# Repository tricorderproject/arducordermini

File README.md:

Arducorder Mini
======

Arducorder Mini -- an Arduino-compatible Open Source Science Tricorder Project  
http://www.tricorderproject.org  
Copyright (C) 2014  Peter Jansen and the Tricorder project  
peter@tricorderproject.org  

*This is a work in progress*

# Introduction

This is the third iteration of the Open Source Science Tricorder prototypes, a series of science tricorder-like devices.  

Unlike the first two prototypes, this version has been designed from the ground up to be easy to manufacture, and to foster a community of open source developers and users.  The firmware is Arduino-compatible through the ChipKit MAX32 platform, and is being designed to provide advanced functionality for scientific use while being easy enough for beginners to meaningfully modify. 

# Concept
It is my deep belief that knowledge brings about positive change. 

We could live in a world where the same instrument that can show a child how much chlorophyll is in a leaf could also show how them much pollution is in the air around us, or given off by one's car. As an educator and a researcher, I feel that if people could easily discover things about their worlds that were also important social topics, that they would then make positive social choices, like reducing their emissions, or petitioning for cleaner industry in their communities. 

By having access to general inexpensive sensing tools, people can learn about healthy leaves, clean air, clouds and the water cycle, energy efficient homes — and visualize abstract concepts like spectra or magnetism. 

As a tool for exploration, we can discover things around us that we don't already know. And that's what it's about. Little discoveries, everywhere.

# Open Source

This project is open hardware and is released under various open licenses.  Please see LICENSES.TXT for details.

# Warning

**DISCLAIMER OF WARRANTIES AND LIMITATION OF LIABILITY.**

UNLESS OTHERWISE SEPARATELY UNDERTAKEN BY THE LICENSOR, TO THE EXTENT POSSIBLE, THE LICENSOR OFFERS THE LICENSED MATERIAL AS-IS AND AS-AVAILABLE, AND MAKES NO REPRESENTATIONS OR WARRANTIES OF ANY KIND CONCERNING THE LICENSED MATERIAL, WHETHER EXPRESS, IMPLIED, STATUTORY, OR OTHER. THIS INCLUDES, WITHOUT LIMITATION, WARRANTIES OF TITLE, MERCHANTABILITY, FITNESS FOR A PARTICULAR PURPOSE, NON-INFRINGEMENT, ABSENCE OF LATENT OR OTHER DEFECTS, ACCURACY, OR THE PRESENCE OR ABSENCE OF ERRORS, WHETHER OR NOT KNOWN OR DISCOVERABLE. WHERE DISCLAIMERS OF WARRANTIES ARE NOT ALLOWED IN FULL OR IN PART, THIS DISCLAIMER MAY NOT APPLY TO YOU.

TO THE EXTENT POSSIBLE, IN NO EVENT WILL THE LICENSOR BE LIABLE TO YOU ON ANY LEGAL THEORY (INCLUDING, WITHOUT LIMITATION, NEGLIGENCE) OR OTHERWISE FOR ANY DIRECT, SPECIAL, INDIRECT, INCIDENTAL, CONSEQUENTIAL, PUNITIVE, EXEMPLARY, OR OTHER LOSSES, COSTS, EXPENSES, OR DAMAGES ARISING OUT OF THIS PUBLIC LICENSE OR USE OF THE LICENSED MATERIAL, EVEN IF THE LICENSOR HAS BEEN ADVISED OF THE POSSIBILITY OF SUCH LOSSES, COSTS, EXPENSES, OR DAMAGES. WHERE A LIMITATION OF LIABILITY IS NOT ALLOWED IN FULL OR IN PART, THIS LIMITATION MAY NOT APPLY TO YOU.

THE DISCLAIMER OF WARRANTIES AND LIMITATION OF LIABILITY PROVIDED ABOVE SHALL BE INTERPRETED IN A MANNER THAT, TO THE EXTENT POSSIBLE, MOST CLOSELY APPROXIMATES AN ABSOLUTE DISCLAIMER AND WAIVER OF ALL LIABILITY.

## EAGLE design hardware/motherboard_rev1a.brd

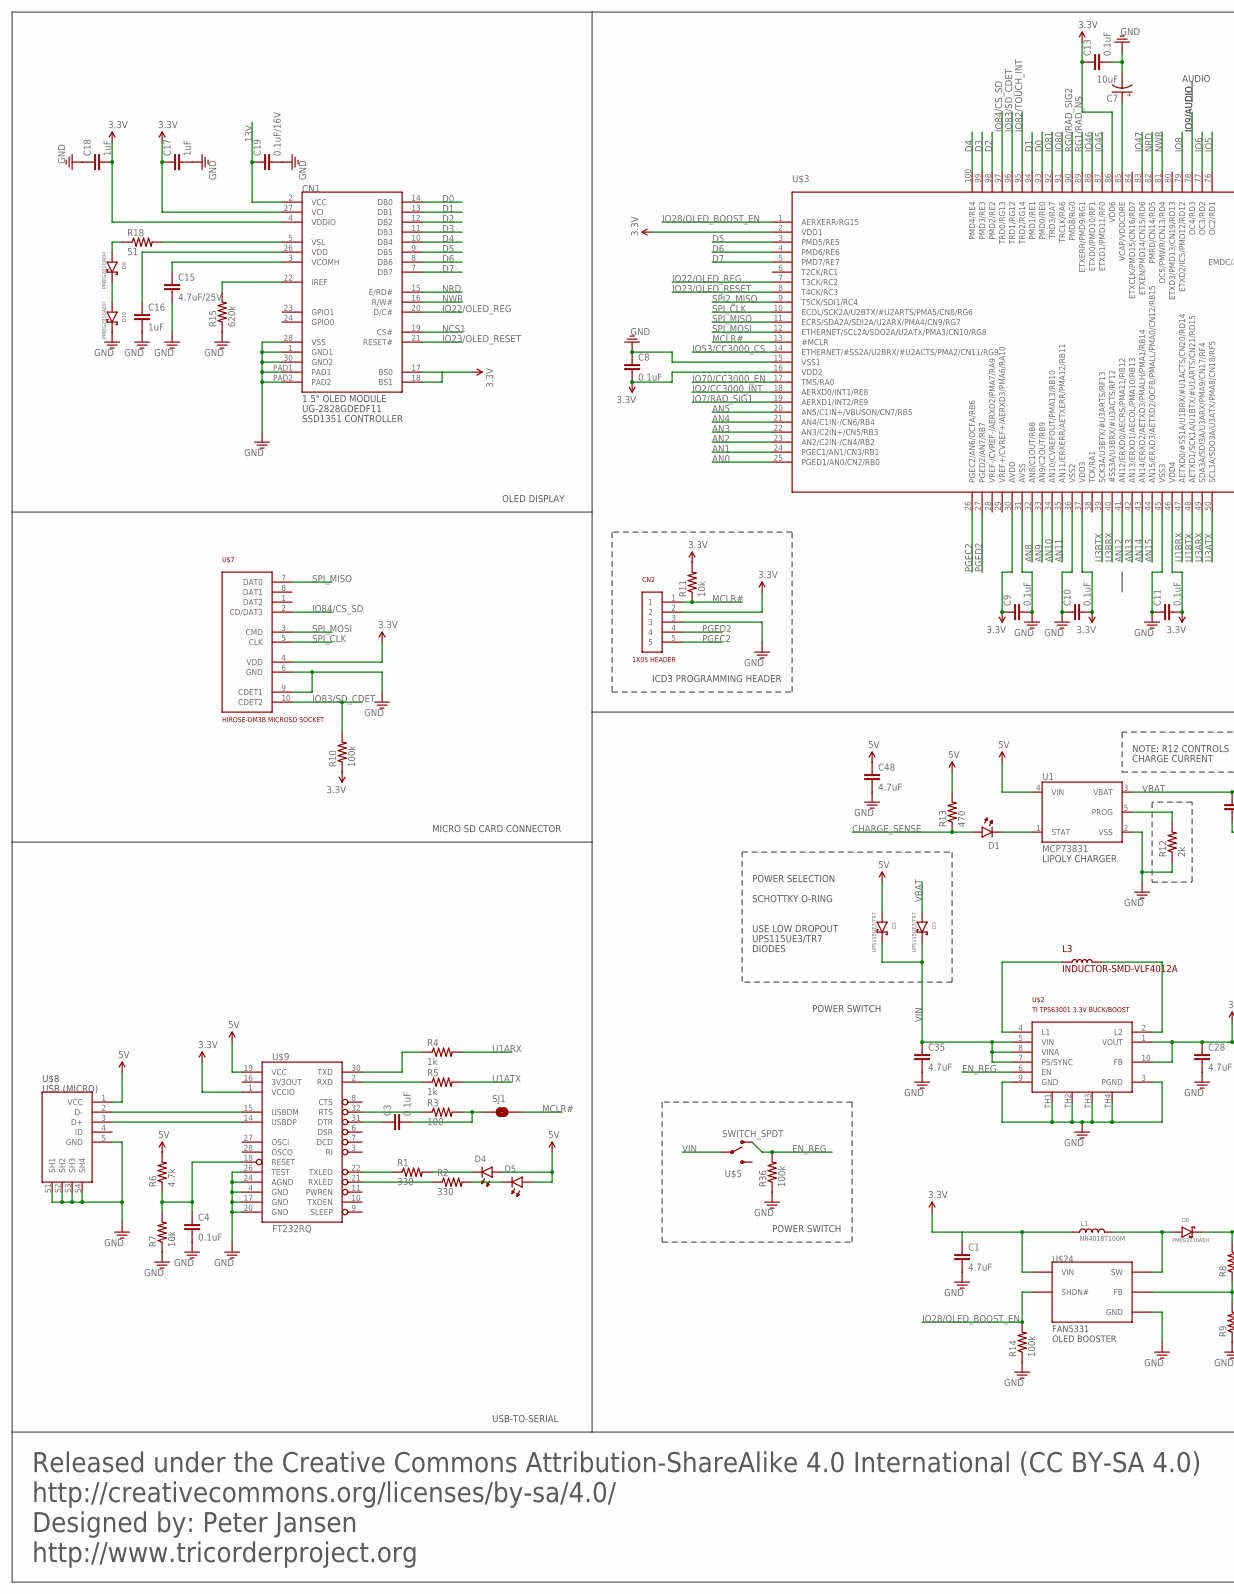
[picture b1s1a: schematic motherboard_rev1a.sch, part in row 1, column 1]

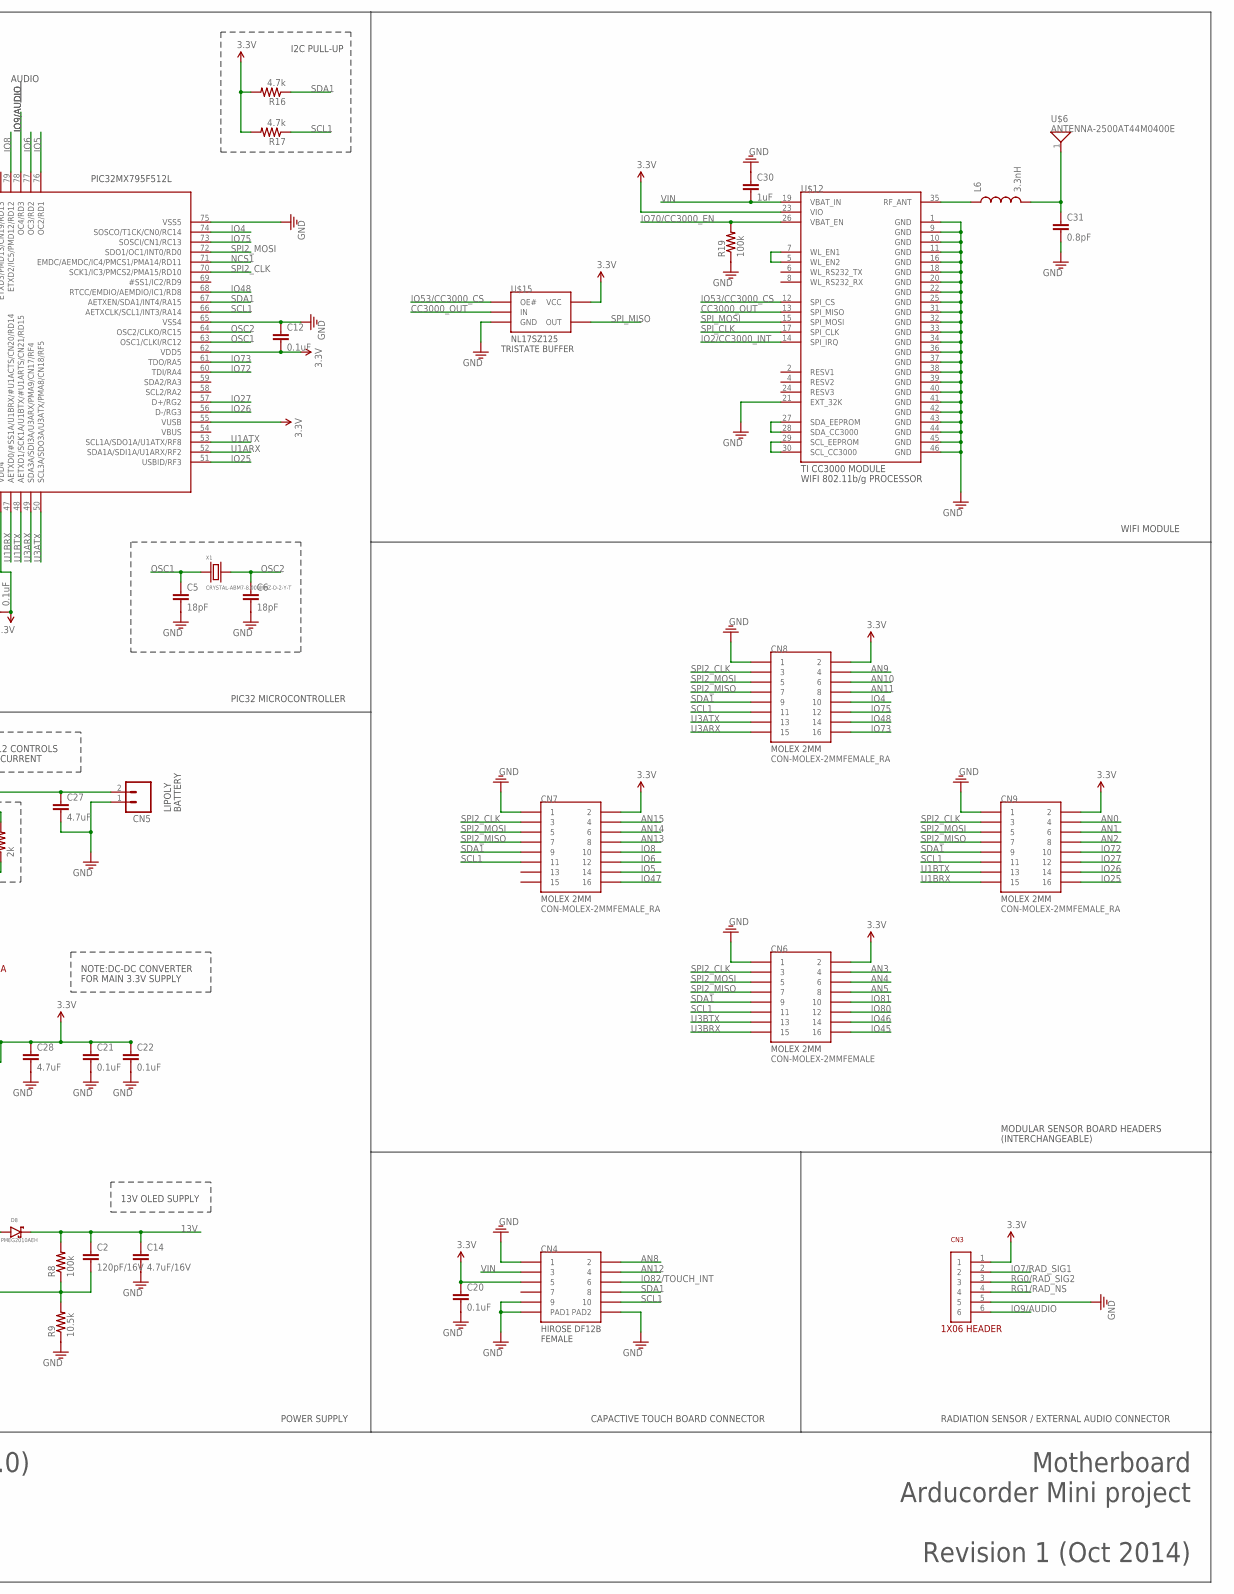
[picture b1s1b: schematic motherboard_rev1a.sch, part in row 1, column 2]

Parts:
C1, C27, C28, C35, C48: 4.7uF; 0603
C2: 120pF/16V; 0603
C3, C4, C8, C9, C10, C11, C12, C13, C20, C21, C22: 0.1uF; 0603
C5, C6: 18pF; 0603
C7: 10uF; EIA3216
C14: 4.7uF/16V; 0603
C15: 4.7uF/25V; 0603
C16, C17, C18, C30: 1uF; 0603
C19: 0.1uF/16V; 0603
C31: 0.8pF; C0402
CN1: UG-2828GDEDF11-1.5OLED; XF2M-3015-1A-1.5LCD
CN2: 1X05
CN3: PHF-106-01-L-S; 1X06
CN4: FEMALE; DF12B(3.0)-10DP-0.5V(86)
CN5: M02-JST-2MM-SMT; JST-2-SMD
CN6: CON-MOLEX-2MMFEMALE; MOLEX-0791091007
CN7, CN8, CN9: CON-MOLEX-2MMFEMALE_RA; MOLEX-87368-1624
D1, D4, D5: 0605-LED; 0603-LED
D2, D3: UPS115UE3/TR7; DO-214BA
D8, D9, D10: PMEG2010AEH; SOD123F
L1: NR4018T100M
L3: INDUCTOR-SMD-VLF4012A; VLF4012A
L6: 3.3nH; C0402
R1, R2: 330; 0603
R3: 100; 0603
R4, R5: 1k; 0603
R6, R16, R17: 4.7k; 0603
R7, R11: 10k; 0603
R8, R10, R14, R19, R36: 100k; 0603
R9: 10.5k; 0603
R12: 2k; 0603
R13: 470; 0603
R15: 620k; 0603
R18: 51; 0603
SJ1: SOLDERJUMPERTRACE; SJ_2S-TRACE
U1: MCP73831; SOT23-5
U$2: TI-TPS63001-3.3V-BUCKBOOST; TPS63001
U$3: PIC32MX795F512L-80I/PF; SQFP-S-14X14-100
U$5: SWITCH_SPDT; KPS-1290
U$6: ANTENNA-2500AT44M0400E; ANT-2500AT44M0400E
U$7: CON-HIROSE-DM3B-MICROSD
U$8: USB-MICROB; FCI-10104110-0001LF
U$9: FT232RQ; QFN-32
U$12: CC3000
U$15: BUFFER-NL17SZ125; TSOP-5
U$24: FAN5331-BOOST; TSOP-5
X1: CRYSTAL-ABM7-8.000MHZ-D-2-Y-T; CYRSTAL-6.0X3.5MM

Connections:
3.3V: C1.1, C8.2, C9.1, C10.2, C11.2, C12.2, C13.1, C17.1, C18.2, C20.1, C21.1, C22.1, C28.1, CN1.4 (VDDIO), CN1.17 (BS0), CN1.18 (BS1), CN1.27 (VCI), CN2.2, CN3.1, CN4.5, CN6.2, CN7.2, CN8.2, CN9.2, L1.2, R10.1, R11.2, R16.2, R17.2, U$2.1 (VOUT), U$2.10 (FB), U$3.2 (VDD1), U$3.16 (VDD2), U$3.30 (AVDD), U$3.37 (VDD3), U$3.46 (VDD4), U$3.55 (VUSB), U$3.62 (VDD5), U$3.86 (VDD6), U$7.4 (VDD), U$9.1 (VCCIO), U$12.23 (VIO), U$15.5 (VCC), U$24.5 (VIN)
5V: C48.1, D2.ANODE, D4.ANODE, D5.ANODE, R6.2, R13.2, U1.4 (VIN), U$8.1 (VCC), U$9.19 (VCC)
13V: C2.1, C14.1, C19.1, CN1.2 (VCC), D8.1 (CATHODE), R8.2
AN0: CN9.4, U$3.25 (PGED1/AN0/CN2/RB0)
AN1: CN9.6, U$3.24 (PGEC1/AN1/CN3/RB1)
AN2: CN9.8, U$3.23 (AN2/C2IN-/CN4/RB2)
AN3: CN6.4, U$3.22 (AN3/C2IN+/CN5/RB3)
AN4: CN6.6, U$3.21 (AN4/C1IN-/CN6/RB4)
AN5: CN6.8, U$3.20 (AN5/C1IN+/VBUSON/CN7/RB5)
AN8: CN4.2, U$3.32 (AN8/C1OUT/RB8)
AN9: CN8.4, U$3.33 (AN9/C2OUT/RB9)
AN10: CN8.6, U$3.34 (AN10/CVREFOUT/PMA13/RB10)
AN11: CN8.8, U$3.35 (AN11/ERXERR/AETXERR/PMA12/RB11)
AN12: CN4.4, U$3.41 (AN12/ERXD0/AECRS/PMA11/RB12)
AN13: CN7.8, U$3.42 (AN13/ERXD1/AECOL/PMA10/RB13)
AN14: CN7.6, U$3.43 (AN14/ERXD2/AETXD3/PMALH/PMA1/RB14)
AN15: CN7.4, U$3.44 (AN15/ERXD3/AETXD2/OCFB/PMALL/PMA0/CN12/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)
CC3000_OUT: U$12.13 (SPI_MISO), U$15.2 (IN)
CHARGE_SENSE: D1.ANODE, R13.1
D0: CN1.14 (DB0), U$3.93 (PMD0/RE0)
D1: CN1.13 (DB1), U$3.94 (PMD1/RE1)
D2: CN1.12 (DB2), U$3.98 (PMD2/RE2)
D3: CN1.11 (DB3), U$3.99 (PMD3/RE3)
D4: CN1.10 (DB4), U$3.100 (PMD4/RE4)
D5: CN1.9 (DB5), U$3.3 (PMD5/RE5)
D6: CN1.8 (DB6), U$3.4 (PMD6/RE6)
D7: CN1.7 (DB7), U$3.5 (PMD7/RE7)
EN_REG: R36.2, U$2.6 (EN), U$5.O
GND: C1.2, C4.2, C5.2, C6.2, C7.C (-), C8.1, C9.2, C10.1, C11.1, C12.1, C13.2, C14.2, C15.2, C16.2, C17.2, C18.1, C19.2, C20.2, C21.2, C22.2, C27.2, C28.2, C30.1, C31.2, C35.2, C48.2, CN1.1 (GND1), CN1.28 (VSS), CN1.30 (GND2), CN1.PAD1, CN1.PAD2, CN2.3, CN3.5, CN4.1, CN4.9, CN4.PAD1, CN4.PAD2, CN5.1 (2), CN6.1, CN7.1, CN8.1, CN9.1, D10.1 (CATHODE), R7.1, R9.1, R12.1, R14.1, R15.1, R19.1, R36.1, U1.2 (VSS), U$2.3 (PGND), U$2.9 (GND), U$2.TH1 (THERM1), U$2.TH2 (THERM2), U$2.TH3 (THERM3), U$2.TH4 (THERM4), U$3.15 (VSS1), U$3.31 (AVSS), U$3.36 (VSS2), U$3.45 (VSS3), U$3.65 (VSS4), U$3.75 (VSS5), U$7.6 (GND), U$7.9 (CDET1), U$8.5 (GND), U$8.S1 (SH1), U$8.S2 (SH2), U$8.S3 (SH3), U$8.S4 (SH4), U$9.4 (GND), U$9.17 (GND), U$9.20 (GND), U$9.24 (AGND), U$9.26 (TEST), U$12.1 (GND), U$12.9 (GND), U$12.10 (GND), U$12.11 (GND), U$12.16 (GND), U$12.18 (GND), U$12.20 (GND), U$12.21 (EXT_32K), U$12.22 (GND), U$12.25 (GND), U$12.31 (GND), U$12.32 (GND), U$12.33 (GND), U$12.34 (GND), U$12.36 (GND), U$12.37 (GND), U$12.38 (GND), U$12.39 (GND), U$12.40 (GND), U$12.41 (GND), U$12.42 (GND), U$12.43 (GND), U$12.44 (GND), U$12.45 (GND), U$12.46 (GND), U$15.3 (GND), U$24.2 (GND)
IO2/CC3000_INT: U$3.18 (AERXD0/INT1/RE8), U$12.14 (SPI_IRQ)
IO4: CN8.10, U$3.74 (SOSCO/T1CK/CN0/RC14)
IO5: CN7.14, U$3.76 (OC2/RD1)
IO6: CN7.12, U$3.77 (OC3/RD2)
IO7/RAD_SIG1: CN3.2, U$3.19 (AERXD1/INT2/RE9)
IO8: CN7.10, U$3.79 (ETXD2/IC5/PMD12/RD12)
IO9/AUDIO: CN3.6, U$3.78 (OC4/RD3)
IO22/OLED_REG: CN1.20 (D/C#), U$3.7 (T3CK/RC2)
IO23/OLED_RESET: CN1.21 (RESET#), U$3.8 (T4CK/RC3)
IO25: CN9.16, U$3.51 (USBID/RF3)
IO26: CN9.14, U$3.56 (D-/RG3)
IO27: CN9.12, U$3.57 (D+/RG2)
IO28/OLED_BOOST_EN: R14.2, U$3.1 (AERXERR/RG15), U$24.4 (SHDN#)
IO45: CN6.16, U$3.87 (ETXD1/PMD11/RF0)
IO46: CN6.14, U$3.88 (ETXD0/PMD10/RF1)
IO47: CN7.16, U$3.83 (ETXEN/PMD14/CN15/RD6)
IO48: CN8.14, U$3.68 (RTCC/EMDIO/AEMDIO/IC1/RD8)
IO53/CC3000_CS: U$3.14 (ETHERNET/#SS2A/U2BRX/#U2ACTS/PMA2/CN11/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), U$12.12 (SPI_CS), U$15.1 (OE#)
IO70/CC3000_EN: R19.2, U$3.17 (TMS/RA0), U$12.26 (VBAT_EN)
IO72: CN9.10, U$3.60 (TDI/RA4)
IO73: CN8.16, U$3.61 (TDO/RA5)
IO75: CN8.12, U$3.73 (SOSCI/CN1/RC13)
IO80: CN6.12, U$3.91 (TRCLK/RA6)
IO81: CN6.10, U$3.92 (TRD3/RA7)
IO82/TOUCH_INT: CN4.6, U$3.95 (TRD2/RG14)
IO83/SD_CDET: R10.2, U$3.96 (TRD1/RG12), U$7.10 (CDET2)
IO84/CS_SD: U$3.97 (TRD0/RG13), U$7.2 (CD/DAT3)
MCLR#: CN2.1, R11.1, SJ1.2, U$3.13 (#MCLR)
unnamed: L3.1, U$2.4 (L1)
unnamed: L3.2, U$2.2 (L2)
unnamed: U$8.2 (D-), U$9.15 (USBDM)
unnamed: U$8.3 (D+), U$9.14 (USBDP)
unnamed: R1.1, U$9.22 (TXLED)
unnamed: R2.1, U$9.21 (RXLED)
unnamed: D4.CATHODE, R1.2
unnamed: D5.CATHODE, R2.2
unnamed: C3.1, U$9.31 (DTR)
unnamed: R3.1, U$9.32 (RTS)
unnamed: C3.2, R3.2, SJ1.1
unnamed: C4.1, R6.1, R7.2, U$9.18 (RESET)
unnamed: R5.1, U$9.2 (RXD)
unnamed: C31.1, L6.2, U$6.1
unnamed: R4.1, U$9.30 (TXD)
unnamed: U$12.27 (SDA_EEPROM), U$12.28 (SDA_CC3000)
unnamed: L6.1, U$12.35 (RF_ANT)
unnamed: C7.A (+), U$3.85 (VCAP/VDDCORE)
unnamed: C15.1, CN1.3 (VCOMH)
unnamed: D8.2 (ANODE), L1.1, U$24.1 (SW)
unnamed: CN1.22 (IREF), R15.2
unnamed: C2.2, R8.1, R9.2, U$24.3 (FB)
unnamed: C16.1, CN1.26 (VDD)
unnamed: D9.1 (CATHODE), D10.2 (ANODE)
unnamed: D9.2 (ANODE), R18.1
unnamed: R12.2, U1.5 (PROG)
unnamed: U$12.29 (SCL_EEPROM), U$12.30 (SCL_CC3000)
unnamed: CN1.5 (VSL), R18.2
unnamed: D1.CATHODE, U1.1 (STAT)
unnamed: U$12.5 (WL_EN2), U$12.7 (WL_EN1)
NCS1: CN1.19 (CS#), U$3.71 (EMDC/AEMDC/IC4/PMCS1/PMA14/RD11)
NRD: CN1.15 (E/RD#), U$3.82 (PMRD/CN14/RD5)
NWR: CN1.16 (R/W#), U$3.81 (OC5/PMWR/CN13/RD4)
OSC1: C5.1, U$3.63 (OSC1/CLKI/RC12), X1.1
OSC2: C6.1, U$3.64 (OSC2/CLKO/RC15), X1.2
PGEC2: CN2.5, U$3.26 (PGEC2/AN6/OCFA/RB6)
PGED2: CN2.4, U$3.27 (PGED2/AN7/RB7)
RG0/RAD_SIG2: CN3.3, U$3.90 (PMD8/RG0)
RG1/RAD_NS: CN3.4, U$3.89 (ETXERR/PMD9/RG1)
SCL1: CN4.10, CN6.11, CN7.11, CN8.11, CN9.11, R17.1, U$3.66 (AETXCLK/SCL1/INT3/RA14)
SDA1: CN4.8, CN6.9, CN7.9, CN8.9, CN9.9, R16.1, U$3.67 (AETXEN/SDA1/INT4/RA15)
SPI2_CLK: CN6.3, CN7.3, CN8.3, CN9.3, U$3.70 (SCK1/IC3/PMCS2/PMA15/RD10)
SPI2_MISO: CN6.7, CN7.7, CN8.7, CN9.7, U$3.9 (T5CK/SDI1/RC4)
SPI2_MOSI: CN6.5, CN7.5, CN8.5, CN9.5, U$3.72 (SDO1/OC1/INT0/RD0)
SPI_CLK: U$3.10 (ECOL/SCK2A/U2BTX/#U2ARTS/PMA5/CN8/RG6), U$7.5 (CLK), U$12.17 (SPI_CLK)
SPI_MISO: U$3.11 (ECRS/SDA2A/SDI2A/U2ARX/PMA4/CN9/RG7), U$7.7 (DAT0), U$15.4 (OUT)
SPI_MOSI: U$3.12 (ETHERNET/SCL2A/SDO2A/U2ATX/PMA3/CN10/RG8), U$7.3 (CMD), U$12.15 (SPI_MOSI)
U1ARX: R4.2, U$3.52 (SDA1A/SDI1A/U1ARX/RF2)
U1ATX: R5.2, U$3.53 (SCL1A/SDO1A/U1ATX/RF8)
U1BRX: CN9.15, U$3.47 (AETXD0/#SS1A/U1BRX/#U1ACTS/CN20/RD14)
U1BTX: CN9.13, U$3.48 (AETXD1/SCK1A/U1BTX/#U1ARTS/CN21/RD15)
U3ARX: CN8.15, U$3.49 (SDA3A/SDI3A/U3ARX/PMA9/CN17/RF4)
U3ATX: CN8.13, U$3.50 (SCL3A/SDO3A/U3ATX/PMA8/CN18/RF5)
U3BRX: CN6.15, U$3.40 (#SS3A/U3BRX/#U3ACTS/RF12)
U3BTX: CN6.13, U$3.39 (SCK3A/U3BTX/#U3ARTS/RF13)
VBAT: C27.1, CN5.2 (1), D3.ANODE, U1.3 (VBAT)
VIN: C30.2, C35.1, CN4.3, D2.CATHODE, D3.CATHODE, U$2.5 (VIN), U$2.7 (PS/SYNC), U$2.8 (VINA), U$5.P, U$12.19 (VBAT_IN)

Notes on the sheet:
NOTE: R12 CONTROLS
CHARGE CURRENT
POWER SELECTION
SCHOTTKY O-RING
USE LOW DROPOUT
UPS115UE3/TR7
DIODES
LIPOLY
POWER SWITCH
AUDIO
Released under the Creative Commons Attribution-ShareAlike 4.0 International (CC BY-SA 4.0)
http://creativecommons.org/licenses/by-sa/4.0/
Designed by: Peter Jansen
http://www.tricorderproject.org
Revision 1 (Oct 2014)
Arducorder Mini project
Motherboard
USB-TO-SERIAL
MICRO SD CARD CONNECTOR
OLED DISPLAY
PIC32 MICROCONTROLLER
POWER SUPPLY
LIPOLY CHARGER
NOTE:DC-DC CONVERTER
FOR MAIN 3.3V SUPPLY
13V OLED SUPPLY
BATTERY
WIFI MODULE
MODULAR SENSOR BOARD HEADERS
(INTERCHANGEABLE)
CAPACTIVE TOUCH BOARD CONNECTOR
RADIATION SENSOR / EXTERNAL AUDIO CONNECTOR
ICD3 PROGRAMMING HEADER
I2C PULL-UP

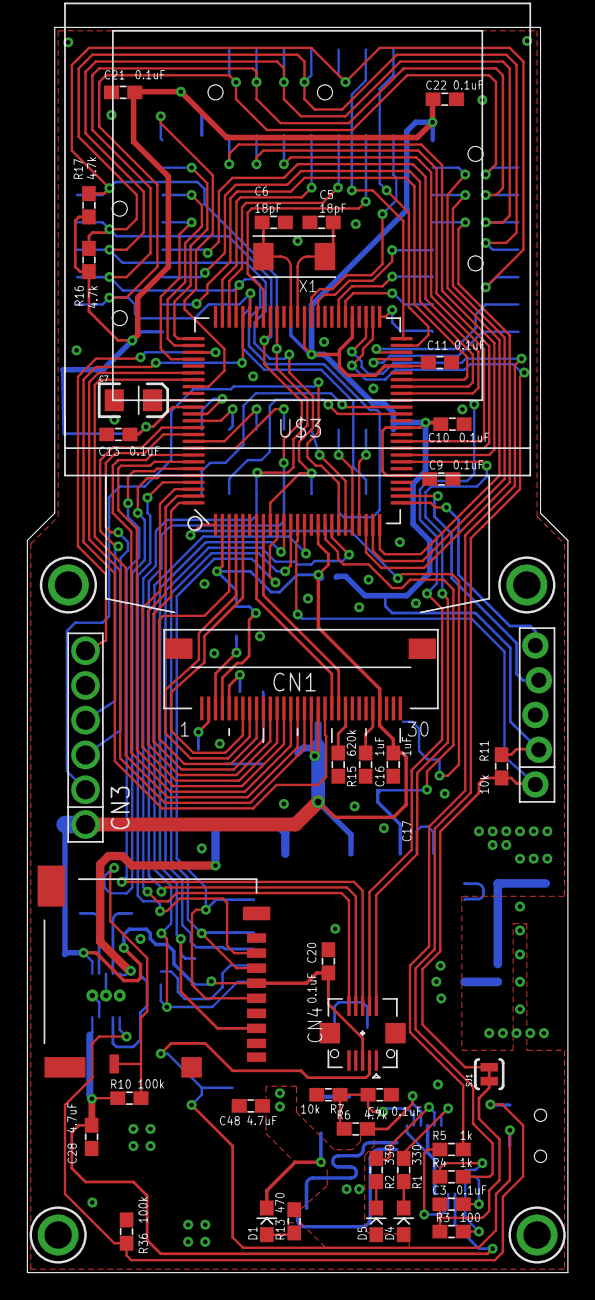
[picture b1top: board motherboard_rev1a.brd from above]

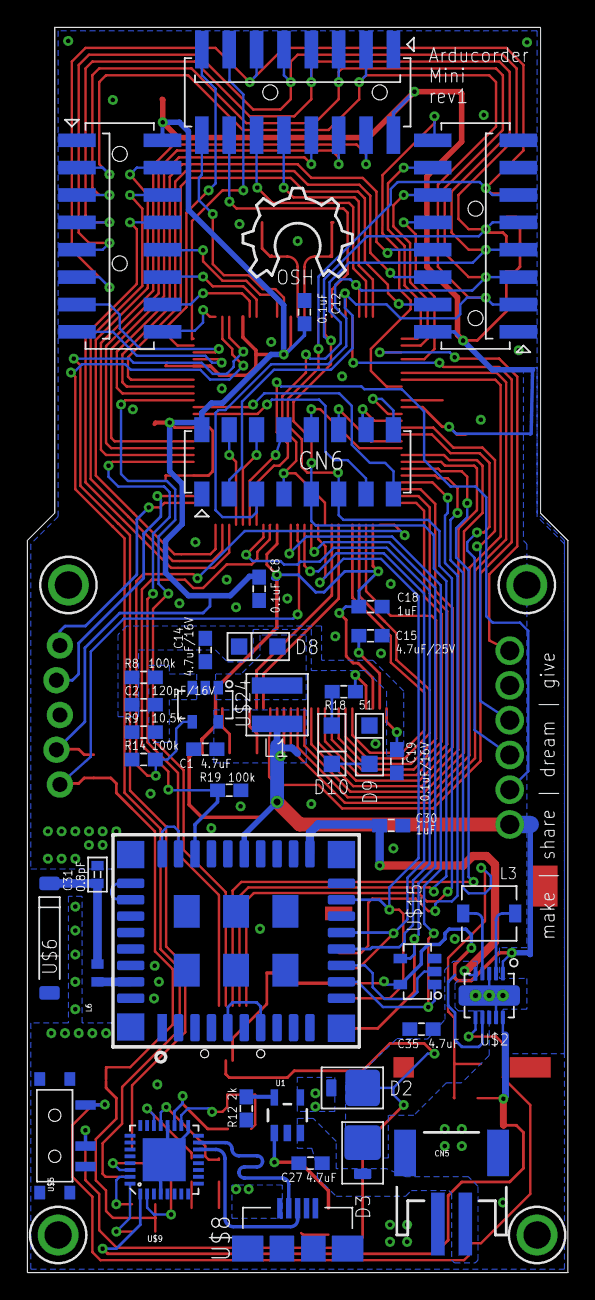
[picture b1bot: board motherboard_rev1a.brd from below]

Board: 2 copper layers, 39.5 x 91.0 mm, 81 parts (40 on the bottom side), 114 nets.

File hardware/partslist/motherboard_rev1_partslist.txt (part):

Partlist

Exported from motherboard_rev1.sch at 27/10/2014 11:52:06 PM

EAGLE Version 6.5.0 Copyright (c) 1988-2013 CadSoft

Assembly variant: 

Part     Value                         Device                        Package                  Library                    Sheet

C1       4.7uF                         CAP0603                       0603                     notes_mark5a               1
C2       120pF/16V                     CAP0603                       0603                     notes_mark5a1              1
C3       0.1uF                         CAP0603                       0603                     notes_mark5a               1
C4       0.1uF                         CAP0603                       0603                     notes_mark5a               1
C5       18pF                          CAP0603                       0603                     notes_mark5a               1
C6       18pF                          CAP0603                       0603                     notes_mark5a               1
C7       10uF                          CAP_POL1206                   EIA3216                  SparkFun-Passives          1
C8       0.1uF                         CAP0603                       0603                     notes_mark5a               1
C9       0.1uF                         CAP0603                       0603                     notes_mark5a               1
C10      0.1uF                         CAP0603                       0603                     notes_mark5a               1
C11      0.1uF                         CAP0603                       0603                     notes_mark5a               1
C12      0.1uF                         CAP0603                       0603                     notes_mark5a               1
C13      0.1uF                         CAP0603                       0603                     notes_mark5a               1
C14      4.7uF/16V                     CAP0603                       0603                     notes_mark5a               1
C15      4.7uF/25V                     CAP0603                       0603                     notes_mark5a               1
C16      1uF                           CAP0603                       0603                     notes_mark5a               1
C17      1uF                           CAP0603                       0603                     notes_mark5a               1
C18      1uF                           CAP0603                       0603                     notes_mark5a               1
C19      0.1uF/16V                     CAP0603                       0603                     notes_mark5a               1
C20      0.1uF                         CAP0603                       0603                     notes_mark5a               1
C21      0.1uF                         CAP0603                       0603                     notes_mark5a               1
C22      0.1uF                         CAP0603                       0603                     notes_mark5a               1
C27      4.7uF                         CAP0603                       0603                     notes_mark5a               1
C28      4.7uF                         CAP0603                       0603                     notes_mark5a               1
C30      1uF                           CAP0603                       0603                     notes_mark5a               1
C31      0.8pF                         CAP0402                       C0402                    notes_mark5a               1
C35      4.7uF                         CAP0603                       0603                     notes_mark5a               1
C48      4.7uF                         CAP0603                       0603                     notes_mark5a               1
CN1      UG-2828GDEDF11-1.5OLED        UG-2828GDEDF11-1.5OLED        XF2M-3015-1A-1.5LCD      notes-arducorder-mini      1
CN2      1X05                          1X05                          1X05                     notes_mark5a               1
CN3      PHF-106-01-L-S                1X06                          1X06                     arm1a                      1
CN4      FEMALE                        CON-HIROSE-DF12FEMALE         DF12B(3.0)-10DP-0.5V(86) notes-arducorder-mini      1
CN5                                    M02-JST-2MM-SMT               JST-2-SMD                SparkFun-Connectors        1
CN6      CON-MOLEX-2MMFEMALE           CON-MOLEX-2MMFEMALE           MOLEX-0791091007         notes-arducorder-mini      1
CN7      CON-MOLEX-2MMFEMALE_RA        CON-MOLEX-2MMFEMALE_RA        MOLEX-87368-1624         notes-arducorder-mini      1
CN8      CON-MOLEX-2MMFEMALE_RA        CON-MOLEX-2MMFEMALE_RA        MOLEX-87368-1624         notes-arducorder-mini      1
CN9      CON-MOLEX-2MMFEMALE_RA        CON-MOLEX-2MMFEMALE_RA        MOLEX-87368-1624         notes-arducorder-mini      1
D1       0605-LED                      0605-LED                      0603-LED                 notes_mark5a               1
D2       UPS115UE3/TR7                 DIODE-SCHOTTKY                DO-214BA                 notes_mark5a               1
D3       UPS115UE3/TR7                 DIODE-SCHOTTKY                DO-214BA                 notes_mark5a               1
D4       0605-LED                      0605-LED                      0603-LED                 notes_mark5a               1
D5       0605-LED                      0605-LED                      0603-LED                 notes_mark5a               1
D8       PMEG2010AEH                   DIODE-SCHOTTKYSOD123F         SOD123F                  notes-arducorder-mini      1
D9       PMEG2010AEH                   DIODE-SCHOTTKYSOD123F         SOD123F                  notes-arducorder-mini      1
D10      PMEG2010AEH                   DIODE-SCHOTTKYSOD123F         SOD123F                  notes-arducorder-mini      1
L1       NR4018T100M                   INDUCTORNR4018T100M           NR4018T100M              notes-arducorder-mini      1
L3       INDUCTOR-SMD-VLF4012A         INDUCTOR-SMD-VLF4012A         VLF4012A                 notes_mark5a               1
L6       3.3nH                         INDUCTOR0402                  C0402                    SparkFun-Passives          1
R1       330                           RESISTOR0603                  0603                     notes_mark5a               1
R2       330                           RESISTOR0603                  0603                     notes_mark5a               1
R3       100                           RESISTOR0603                  0603                     notes_mark5a               1
R4       1k                            RESISTOR0603                  0603                     notes_mark5a               1
R5       1k                            RESISTOR0603                  0603                     notes_mark5a               1
R6       4.7k                          RESISTOR0603                  0603                     notes_mark5a               1
R7       10k                           RESISTOR0603                  0603                     notes_mark5a               1
R8       100k                          RESISTOR0603                  0603                     notes_mark5a1              1
R9       10.5k                         RESISTOR0603                  0603                     notes_mark5a1              1
R10      100k                          RESISTOR0603                  0603                     notes_mark5a               1
R11      10k                           RESISTOR0603                  0603                     notes_mark5a               1
R12      2k                            RESISTOR0603                  0603                     notes_mark5a               1
R13      470                           RESISTOR0603                  0603                     notes_mark5a               1
R14      100k                          RESISTOR0603                  0603                     notes_mark5a1              1
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
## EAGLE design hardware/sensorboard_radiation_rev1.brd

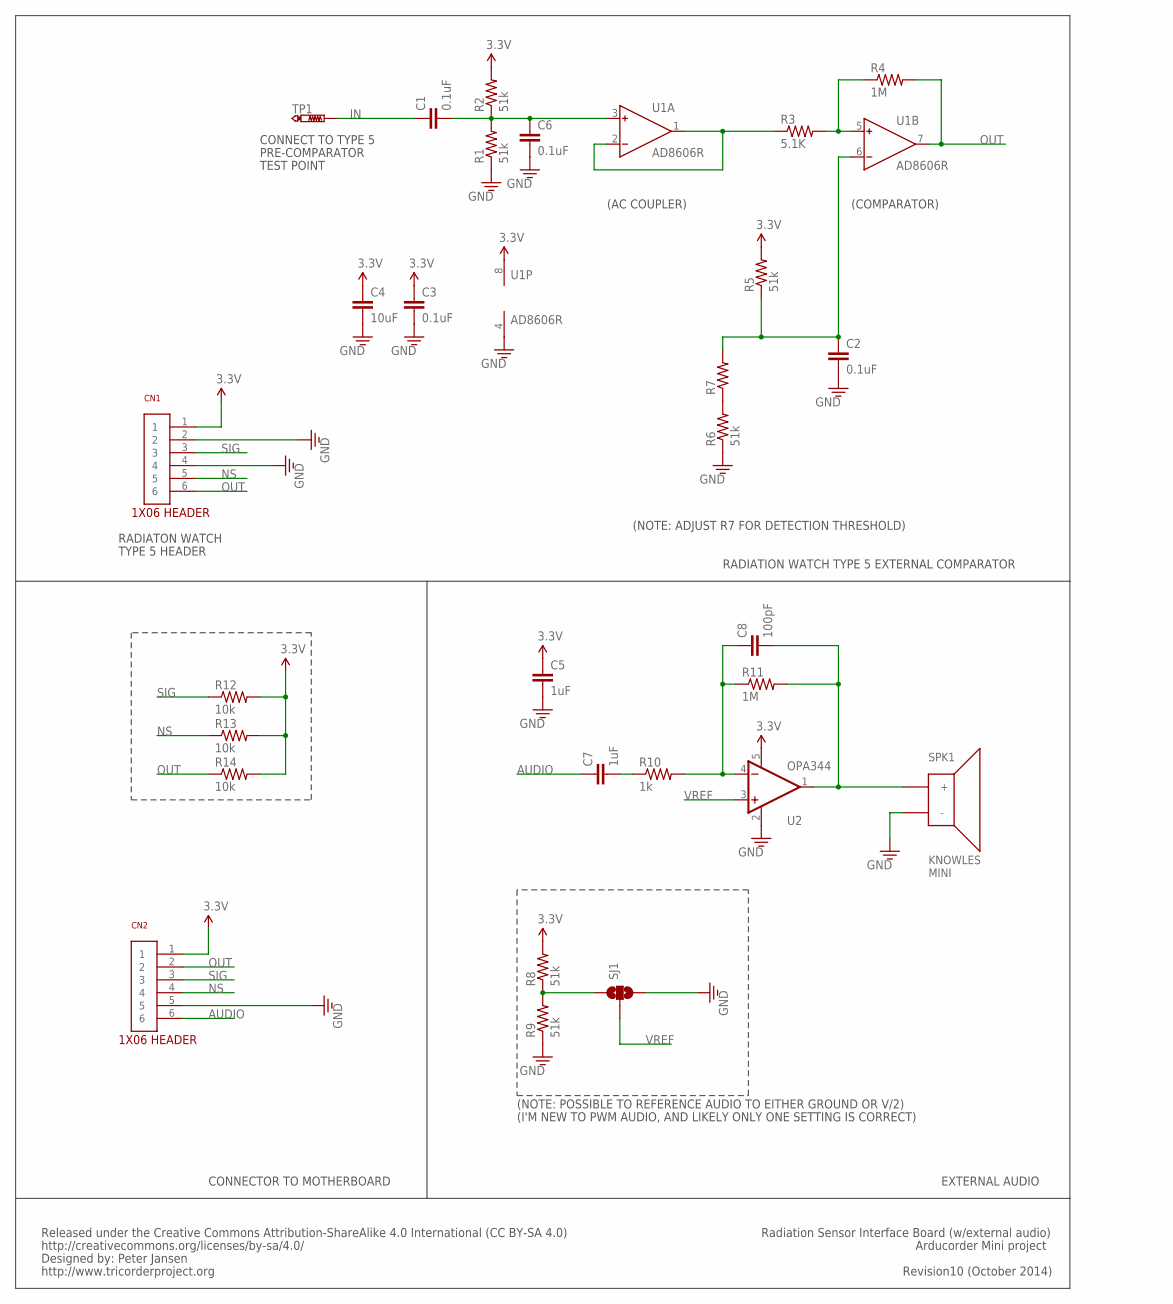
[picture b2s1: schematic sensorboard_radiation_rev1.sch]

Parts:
C1, C2, C3, C6: 0.1uF; 0603
C4: 10uF; 0603
C5, C7: 1uF; 0603
C8: 100pF; 0603
CN1: 1X06
CN2: PHT-106-01-L-S; 1X06
R1, R2, R5, R6, R8, R9: 51k; 0603
R3: 5.1K; 0603
R4, R11: 1M; 0603
R7: RESISTOR0603; 0603
R10: 1k; 0603
R12, R13, R14: 10k; 0603
SJ1: SOLDERJUMPER_2WAYPASTE1&2; SJ_3_PASTE1&2
SPK1: KNOWLES-MINI-SPEAKER
TP1: PTR1PAD1-13; P1-13
U1: AD8606R; SO8
U2: OPA344; SOT23-5

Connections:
3.3V: C3.1, C4.1, C5.1, CN1.1, CN2.1, R2.2, R5.2, R8.2, R12.2, R13.2, R14.2, U1.8 (V+), U2.5 (V+)
ADMP_OUT: C8.2, R11.2, SPK1.POS (+), U2.1 (OUT)
AUDIO: C7.1, CN2.6
GND: C2.2, C3.2, C4.2, C5.2, C6.2, CN1.2, CN1.4, CN2.5, R1.1, R6.1, R9.1, SJ1.3, SPK1.NEG (-), U1.4 (V-), U2.2 (V-)
IN: C1.1, TP1.TP
unnamed: R6.2, R7.1
unnamed: C1.2, C6.1, R1.2, R2.1, U1.3 (IN+)
unnamed: R3.1, U1.1 (OUT), U1.2 (IN-)
unnamed: R3.2, R4.1, U1.5 (IN+)
unnamed: C2.1, R5.1, R7.2, U1.6 (IN-)
unnamed: C7.2, R10.1
unnamed: C8.1, R10.2, R11.1, U2.4 (-IN)
NS: CN1.5, CN2.4, R13.1
OUT: CN1.6, CN2.2, R4.2, R14.1, U1.7 (OUT)
SIG: CN1.3, CN2.3, R12.1
VREF: SJ1.2, U2.3 (+IN)
VREF1: R8.1, R9.2, SJ1.1

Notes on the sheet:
(AC COUPLER)
(COMPARATOR)
CONNECT TO TYPE 5
PRE-COMPARATOR
TEST POINT
RADIATON WATCH
TYPE 5 HEADER
(NOTE: ADJUST R7 FOR DETECTION THRESHOLD)
(NOTE: POSSIBLE TO REFERENCE AUDIO TO EITHER GROUND OR V/2)
Released under the Creative Commons Attribution-ShareAlike 4.0 International (CC BY-SA 4.0)
http://creativecommons.org/licenses/by-sa/4.0/
Designed by: Peter Jansen
http://www.tricorderproject.org
Revision10 (October 2014)
Arducorder Mini project
Radiation Sensor Interface Board (w/external audio)
(I'M NEW TO PWM AUDIO, AND LIKELY ONLY ONE SETTING IS CORRECT)
EXTERNAL AUDIO
CONNECTOR TO MOTHERBOARD
RADIATION WATCH TYPE 5 EXTERNAL COMPARATOR

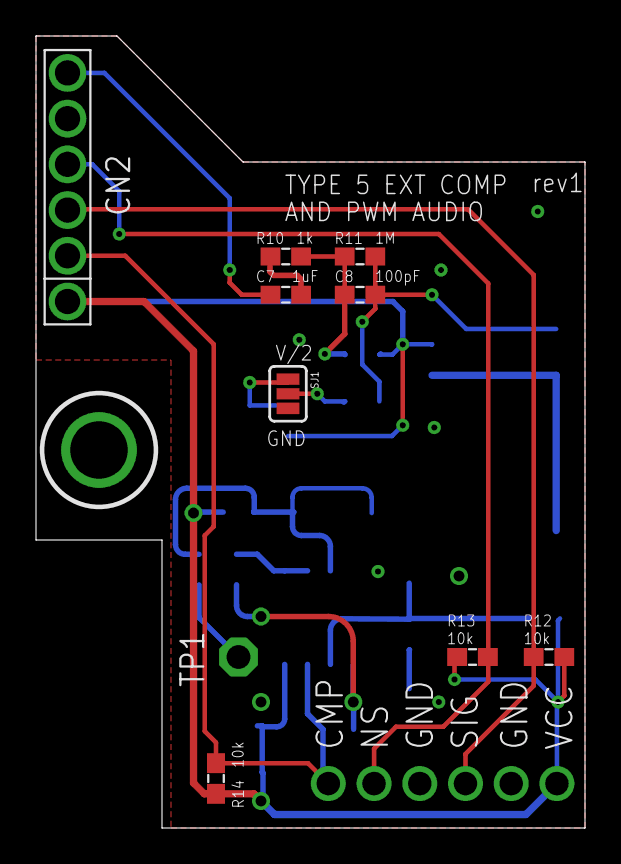
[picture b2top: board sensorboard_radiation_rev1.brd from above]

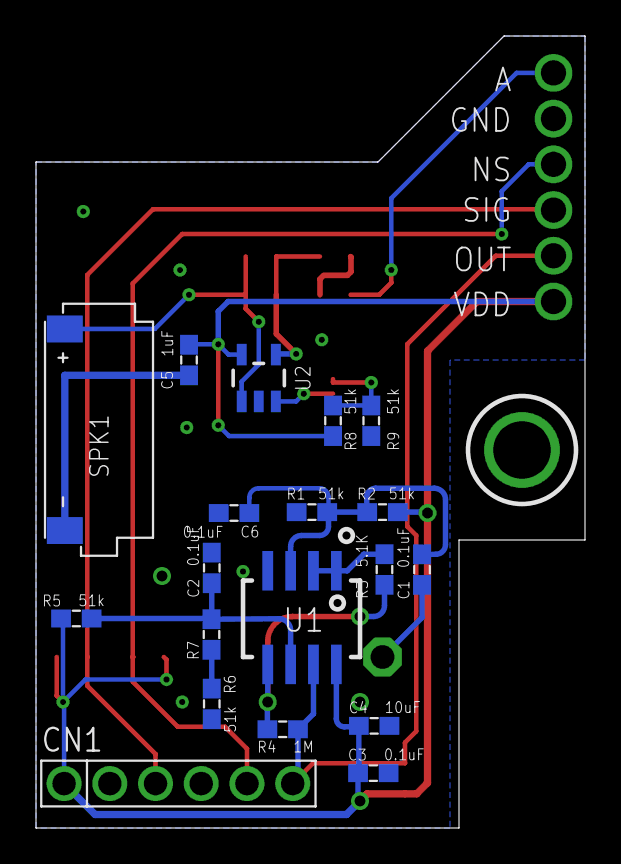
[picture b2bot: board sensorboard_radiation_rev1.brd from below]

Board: 2 copper layers, 30.5 x 44.0 mm, 29 parts (19 on the bottom side), 17 nets.

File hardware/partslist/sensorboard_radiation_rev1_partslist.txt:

Partlist

Exported from sensorboard_radiation_rev1.sch at 27/10/2014 11:53:37 PM

EAGLE Version 6.5.0 Copyright (c) 1988-2013 CadSoft

Assembly variant: 

Part     Value                Device                    Package              Library               Sheet

C1       0.1uF                CAP0603                   0603                 arm                   1
C2       0.1uF                CAP0603                   0603                 arm                   1
C3       0.1uF                CAP0603                   0603                 arm                   1
C4       10uF                 CAP0603                   0603                 arm                   1
C5       1uF                  CAP0603                   0603                 notes_mark5a          1
C6       0.1uF                CAP0603                   0603                 arm                   1
C7       1uF                  CAP0603                   0603                 notes_mark5a          1
C8       100pF                CAP0603                   0603                 notes_mark5a          1
CN1      1X06                 1X06                      1X06                 arm                   1
CN2      PHT-106-01-L-S       1X06                      1X06                 arm1a                 1
R1       51k                  RESISTOR0603              0603                 arm                   1
R2       51k                  RESISTOR0603              0603                 arm                   1
R3       5.1K                 RESISTOR0603              0603                 arm                   1
R4       1M                   RESISTOR0603              0603                 arm                   1
R5       51k                  RESISTOR0603              0603                 arm                   1
R6       51k                  RESISTOR0603              0603                 arm                   1
R7                            RESISTOR0603              0603                 arm                   1
R8       51k                  RESISTOR0603              0603                 notes_mark5a          1
R9       51k                  RESISTOR0603              0603                 notes_mark5a          1
R10      1k                   RESISTOR0603              0603                 notes_mark5a          1
R11      1M                   RESISTOR0603              0603                 notes_mark5a          1
R12      10k                  RESISTOR0603              0603                 arm                   1
R13      10k                  RESISTOR0603              0603                 arm                   1
R14      10k                  RESISTOR0603              0603                 arm                   1
SJ1                           SOLDERJUMPER_2WAYPASTE1&2 SJ_3_PASTE1&2        SparkFun-Passives     1
SPK1     KNOWLES-MINI-SPEAKER KNOWLES-MINI-SPEAKER      KNOWLES-MINI-SPEAKER notes-arducorder-mini 1
TP1      PTR1PAD1-13          PTR1PAD1-13               P1-13                testpad               1
U1       AD8606R              AD8607R                   SO8                  analog-devices        1
U2       OPA344               OPA344                    SOT23-5              SparkFun-AnalogIC     1

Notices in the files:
parts and their libraries:
SparkFun-DigitalIC: Licensing: CC v3.0 Share-Alike You are welcome to use this library for commercial purposes.
SparkFun-Electromechanical: Licensing: Creative Commons ShareAlike 4.0 International - https://creativecommons.org/licenses/by-sa/4.0
